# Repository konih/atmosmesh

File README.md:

<h1 align="center">AtmosMesh</h1>

<p align="center"><em>Local air sensing, connected as a mesh.</em></p>

<p align="center">

</p>

AtmosMesh is a family of local air-sensing firmware products, now spanning several product
variants (v1, Grove v1.5, Aqua, Room, Spot); none supersedes another.

## Firmware products

| Product | Product ID | Product variant | Controller | Sensor/display scope | Canonical build |
| --- | --- | --- | --- | --- | --- |
| **AtmosMesh v1** — **ARCHIVED** (D-034; physical station disassembled 2026-08-31) | `atmosmesh-v1` | `esp32-full-station` | ESP32-WROOM-32 | Full station: SSD1306, BMP280, AM2302, SDS011, MQ135, PIR/beeper, optional VEML7700, MQTT | `task build-v1` (not part of `task build-all`) |
| **AtmosMesh Grove v1.5** | `atmosmesh-grove-v1.5` | `atmosmesh-v1.5` | ESP8266EX / 4 MB NodeMCU-style board | Compact node: 128×32 SSD1306, BMP180, DHT11, uncalibrated D7 RC light, D0/D6 status LED, duty-cycled raw YL-38 ADC, MQTT | `task build-v1-5` |

The products share one PlatformIO project and host-tested core, with explicit composition roots
instead of copied firmware trees. See [ADR-0001](docs/adr/0001-multi-product-firmware-composition.md).

AtmosMesh v1 is **archived, not deleted** ([D-034](agent-context/decisions.md)): the physical
station was disassembled and its code/mentions are retired from the live fleet, but the source,
its tests, and the shared MQTT contract/composition pattern it established remain in the repo.
It was never a finished product — its wiring was never fully approved for unattended or
mains-powered use — and it is **not** a certified health, fire, gas, or life-safety instrument.

## AtmosMesh v1 measurements

| Sensor | Quantity | Notes |
| --- | --- | --- |
| SDS011 | PM2.5, PM10 | UART2 only (GPIO16/17). 5 V heater, 3.3 V UART |
| AM2302 / DHT22 | Temperature, humidity | GPIO18, 3V3 |
| BMP280 | Pressure, temperature | I²C 0x76 on GPIO21/19, 3V3 |
| Mini OLED (D-001) | Local live page | I²C 0x3C, SDA GPIO5, SCL GPIO4, **3V3 only** |
| MQ135 | Relative gas trend | Analog GPIO34 through a divider. **Never labelled CO₂ or ppm** |
| VEML7700 | Illuminance | Optional, I²C 0x10 on the BMP280 bus. Not fitted yet |
| PIR + beeper | Occupancy cue | GPIO33 / GPIO25 |

```text
SDS011 ─┐
AM2302 ─┤
BMP280 ─┼─> ESP32 ── OLED (local)
MQ135  ─┤       └─ MQTT (planned) ──> Mosquitto ──> Home Assistant
VEML   ─┘                         └─ metrics ─> Prometheus ─> Grafana
```

## Safety (read this first)

- ESP32 GPIOs and the `3V3` pin are **not 5 V tolerant**.
- SDS011 and MQ135 take **5 V power**; their *signals* stay at 3.3 V.
- SDS011 is **UART2 only**. Never GPIO1/TX0 or GPIO3/RX0 — those are the USB-UART
  used by `task flash` / `task monitor`.
- MQ135 analog goes through a measured divider before GPIO34. The live breadboard
  is 10 kΩ series + 20 kΩ to GND.
- Open mains PCBs stay off the breadboard and must be enclosed before they are
  energised. Mains switching is out of scope.
- Confirm every module's markings before you copy a pin table from this repo.

Full rules: [`AGENTS.md`](AGENTS.md) and [`docs/hardware/power.md`](docs/hardware/power.md).

## Quick start

Host tests need PlatformIO and Python 3.11 or 3.12 (not Homebrew 3.14):

```bash
task bootstrap-agent-python   # creates .venv with pyserial + esptool
task test                     # native Unity tests (no hardware)
task build-all                # both first-class product images
task build-v1                 # AtmosMesh v1 / ESP32
task build-v1-5               # AtmosMesh Grove v1.5 / ESP8266
```

Canonical device actions are `task flash-v1`, `task monitor-v1`, `task flash-v1-5`, and
`task monitor-v1-5`. Existing `build`/`flash`/`monitor` and `*-grove` tasks remain compatibility
aliases. Override the serial port with `ESP_PORT=/dev/…`.

Do not run `python -m esptool` with system Python. Direct wrapper: `./scripts/esp-tool version`.

Firmware details, OLED constructor, and the live pin map:
[`firmware/README.md`](firmware/README.md).

## Hardware

| Path | What |
| --- | --- |
| [`docs/hardware/inventory.md`](docs/hardware/inventory.md) | Confirmed parts and open questions |
| [`docs/elektronik-inventar.md`](docs/elektronik-inventar.md) | Full electronics stock inventory, including parts not currently assigned to a product |
| [`docs/hardware/datasheets/`](docs/hardware/datasheets/README.md) | Manufacturer datasheets and retained kit manuals |
| [`docs/hardware/power.md`](docs/hardware/power.md) | 5 V / 3.3 V domains |
| [`docs/hardware/oscilloscope-hantek-dso2d15.md`](docs/hardware/oscilloscope-hantek-dso2d15.md) | Bench scope: panel, probe setup, and the ripple / I²C / UART / rail recipes |
| [`hardware/kicad/`](hardware/kicad/README.md) | Bench carrier (KiCad 10): OLED, sensors, extras strip, fully routed. **Do not fabricate** until DevKit pin order is photographed |

The carrier board uses a **10 k / 15 k** MQ135 divider (3.0 V max on GPIO34).
Firmware still matches the **breadboard 10 k / 20 k** until that board replaces
the breadboard.

## Repository layout

| Path | Purpose |
| --- | --- |
| `firmware/` | One PlatformIO project, explicit product roots, shared core and native tests |
| `docs/adr/` | Architecture decision records |
| `docs/history/` | Superseded project notes and concept artifacts retained for provenance |
| `hardware/kicad/` | Bench-station carrier schematic and PCB |
| `docs/` | Architecture, hardware facts, datasheets |
| `deploy/` | Kubernetes / home-automation config (not packaged yet) |
| `tests/` | Host-side checks |
| `agent-context/` | Stories, decisions, and live session notes |
| `AGENTS.md` | Safety boundaries and workflow for humans and agents |

## Status

AtmosMesh v1 bench firmware drives the OLED (U8g2 SSD1306 ALT0), BMP280, AM2302,
SDS011 UART2, MQ135 ADC, PIR, and beeper. MQTT, Home Assistant, and the cluster
path are still ahead. Grove v1.5 hardware has runtime communication evidence for BMP180 and DHT11;
OLED controller initialization passed but pixels need visual confirmation. Cooperative D7 RC light
timing and Grove MQTT/HA discovery are implemented and host/build-tested. Reviewed Grove soil
firmware has produced two raw ADC 214 cycles about 30 seconds apart. The installed D6 red / D0
green LED is operator-confirmed common-anode; soil direction/threshold calibration, switched-rail
electrical behavior, MQTT receipt and OLED pixels remain unconfirmed
([roadmap](agent-context/roadmap.md)).

## License and contributors

[MIT](LICENSE). People: [CONTRIBUTORS.md](CONTRIBUTORS.md). Security:
[SECURITY.md](SECURITY.md).

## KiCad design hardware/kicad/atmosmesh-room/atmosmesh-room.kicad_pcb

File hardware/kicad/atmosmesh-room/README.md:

# AtmosMesh Room carrier — provisional design

**DO NOT ENERGISE THIS BOARD YET.** The controller and every module connector order are now
identified, but no supply voltage or output swing has been measured on the 5 V modules. This project is a protected, reviewable starting point, not a wiring
approval.

The controller is the **ideaspark ESP32 1.14 inch TFT LCD board** (ESP32-WROOM-32), confirmed from
[`docs/hardware/ideaspark-esp32-tft-pinout.png`](../../../docs/hardware/ideaspark-esp32-tft-pinout.png).
Its 30 pins and their order are therefore no longer provisional: pads 1–15 are the left column and
16–30 the right column, both counted from the USB/button end. What remains unmeasured is the
physical **row spacing**: 25.4 mm is still an assumption, so MEASURE THE ROW SPACING before
cutting a socket or committing a hole pattern.

**The integrated display is SPI, not I²C.** It occupies GPIO23 (MOSI), GPIO18 (SCLK), GPIO15 (CS),
GPIO2 (DC), GPIO4 (RST) and GPIO32 (backlight). GPIO21/22 carry no onboard device, so the carrier
supplies the only I²C pull-ups it has.

## Files

| File | Purpose |
| --- | --- |
| `atmosmesh-room.kicad_pro` | KiCad 10 project; open this file |
| `atmosmesh-room.kicad_sch` | Reviewable electrical contract |
| `atmosmesh-room.kicad_pcb` | **Parked.** Kept only as a netlist/silkscreen cross-check — not the build target |
| `perfboard.md` | **The build target**: 31×27 hole plan, orientation rules and build order |
| `atmosmesh-room-perfboard-drawing.svg` | Zoomable front, mirrored back and logical wiring planning drawing |
| `atmosmesh-room-perfboard-drawing.png` | Rendered preview of the planning drawing |
| `validate_room_perfboard.py` | Deterministic structural check on the perfboard plan |
| `room.pretty/`, `fp-lib-table`, `sym-lib-table` | Local THT library contract |
| `BOM.csv` | Values, fitting policy and verification notes |
| `wiring.md` | Connector contract and staged pre-power checks |
| `validate_room_carrier.py` | Deterministic structural safety check |
| `generate_project.py` | Reproducible project generator; KiCad source remains editable |
| `requirements-generator.txt` | Pinned generator-only Python dependency |

## Safety architecture

- ESP32 GPIO and `3V3` must **never receive 5 V**.
- **Never wire GPIO23, 18, 15, 2, 4 or 32** — the dev board's own TFT drives them. GPIO12 is the
  flash-voltage strap (high at boot can stop the board starting) and GPIO1/GPIO3 are the CP2102
  USB-UART used by `task flash` and `task monitor`. `generate_project.py` refuses to emit a net on
  any of them and `validate_room_carrier.py` fails if one appears.
- GPIO21/SDA and GPIO22/SCL reach the external sensor branch through 330 Ω series resistors. Those
  resistors limit fault current and damp edges; they are not a measurement noise source.
- `R_PU_SDA` and `R_PU_SCL` (3.3 kΩ to 3.3 V) are the bus pull-ups. They are required because the
  display is SPI: nothing on the controller board pulls I²C up. They sit on the sensor side of the
  330 Ω resistors so the series resistance stays a fault limit rather than part of the pull-up
  divider. With both breakouts populated the parallel result is roughly 2.0 kΩ, about 1.6 mA at
  3.3 V, inside the I²C 3 mA sink limit, so they stay fitted rather than DNP. Every resistor value
  on this board is justified in `wiring.md`'s sizing table.
- Both sensors receive direct 3.3 V and local 220 nF decoupling. There is deliberately no diode or
  resistor in a sensor supply: a breakout's pull-ups reference its own VDD, so dropping sensor VDD
  drags the pull-ups down with it and buys nothing, while adding a droop path under the SHT41's
  measurement current bursts. The build uses 100 nF for `C1`, `C3`, `C4`
  and `C7` — the confirmed ceramic stock value, inside D-022's own 47–220 nF range.
- The confirmed five-pin VEML7700 connector is `VIN`, `3Vo`, `GND`, `SCL`, `SDA`: `VIN` receives
  3.3 V and `3Vo` is regulator output and remains NC.
- PIR power can come only from a confirmed USB/5 V pin, through `JP_PIR_5V` which is **DEFAULT
  OPEN**, then a 1N5819. PIR OUT drives a 2N3904 through 10 kΩ; GPIO33 sees only the collector and a
  10 kΩ pull-up to 3.3 V. Motion logic is active-low.
- The buzzer is a confirmed Keyes 3-pin module, header order `S`/`VCC`/`−`. GPIO25 drives `S`
  directly through `R_BEEP_S` 100 Ω, active HIGH, exactly as AtmosMesh v1 drives the same part. The
  low-side NPN and flyback diode are gone because the transducer is **self-oscillating inside the
  can** — the breakout PCB carries no parts, so the middle `VCC` pin is a no-op and GPIO25 sources
  the whole operating current. The evidence is that v1 sounds this part with a bare 50 ms DC
  `digitalWrite(HIGH)`, which neither a piezo disc nor a passive coil can do. That type is inferred,
  not measured: one ohmmeter reading across `S` and `−` settles it, and `R_BEEP_S` is **never
  raised** — see the table in `wiring.md` before changing anything.
- `JP_5V_SRC` selects where `+5V_DOMAIN` comes from: the board's `VIN` (pins 1–2) or an external
  bench supply on `J_5V_EXT` (pins 2–3). A 3-pin header takes exactly one shunt, so the two sources
  can never be bridged back into the host's USB port. Use the external, current-limited supply for
  first power-up and whenever the SDS011 fan runs.
- The SDS011 takes 5 V through `JP_SDS_5V`, **DEFAULT OPEN**, with **no series diode**: its minimum
  is 4.7 V and a Schottky at fan current drops below that. Its UART is crossed — sensor TXD to
  GPIO16/RX2, GPIO17/TX2 to sensor RXD — each through a 1 kΩ series resistor that bounds a driver
  fight to about 3.3 mA. The generator refuses both a straight-through UART and a diode on that
  rail.
- Three indicator LEDs show which domains are live. `D_LED_SDS` and `D_LED_PIR` draw **through**
  their own default-open jumpers, so a lit LED is direct evidence that the jumper it reports on is
  closed. Use red or green: a blue or white LED's ~3.0 V forward drop leaves too little across
  `R_LED_3V3` on the 3.3 V rail.
- No Zener clamp is used. This is now positively evidenced rather than assumed: the Zener
  assortment in `docs/elektronik-inventar.md` is the 1N47xx series starting at **1N4733 = 5.1 V**,
  which clamps far too late to protect a 3.3 V GPIO. A 3.3 V part (1N4728) is not held.

## The build target is perfboard

The operator builds this by hand on a **31 × 27 hole** perfboard, so no board is fabricated. The
schematic is the electrical contract and [`perfboard.md`](perfboard.md) is the build plan.

`atmosmesh-room.kicad_pcb` is **parked**: it is still generated from the netlist and still carries
the safety silkscreen, which is why its checks remain in `validate_room_carrier.py`, but its
placement is not maintained as a fabrication candidate. Do not order it.

## Placement and routing state

The VEML7700 sits at a board edge and must be optically shielded from the TFT backlight. The SHT41 sits at
the opposite ventilated edge, away from the ESP32 regulator, PIR electronics and buzzer. The 5 V
PIR block is fenced at the right edge. The antenna clearance is marked on `User.Drawings` and silk;
its final copper keepout/overhang cannot be fixed until the exact board orientation is photographed.

Copper is intentionally unrouted because the Ideaspark row spacing and orientation, plus each
module connector order, are unverified. This prevents a plausible-looking provisional drawing
from being mistaken for a fabrication-ready board. Do not "finish the ratsnest" by assuming a
generic ESP32 DevKit image.

The complete net table, double-sided through-hole placement guidance, assembly order, unpowered
checks, staged commissioning and stop conditions are in [`wiring.md`](wiring.md).

## Validation

From this directory:

```sh
python3.12 -m venv .generator-venv
.generator-venv/bin/pip install -r requirements-generator.txt
.generator-venv/bin/python generate_project.py
python3 validate_room_carrier.py
kicad-cli sch erc --severity-all --exit-code-violations \
  -o atmosmesh-room-erc.rpt atmosmesh-room.kicad_sch
kicad-cli pcb drc --severity-all --schematic-parity --refill-zones \
  -o atmosmesh-room-drc.rpt atmosmesh-room.kicad_pcb
kicad-cli sch export pdf -o atmosmesh-room-schematic.pdf atmosmesh-room.kicad_sch
```

DRC reports the deliberately unrouted nets as unconnected; schematic parity must remain clean and
there must be no other DRC violation. Routing stays blocked until the exact physical parts are
verified.

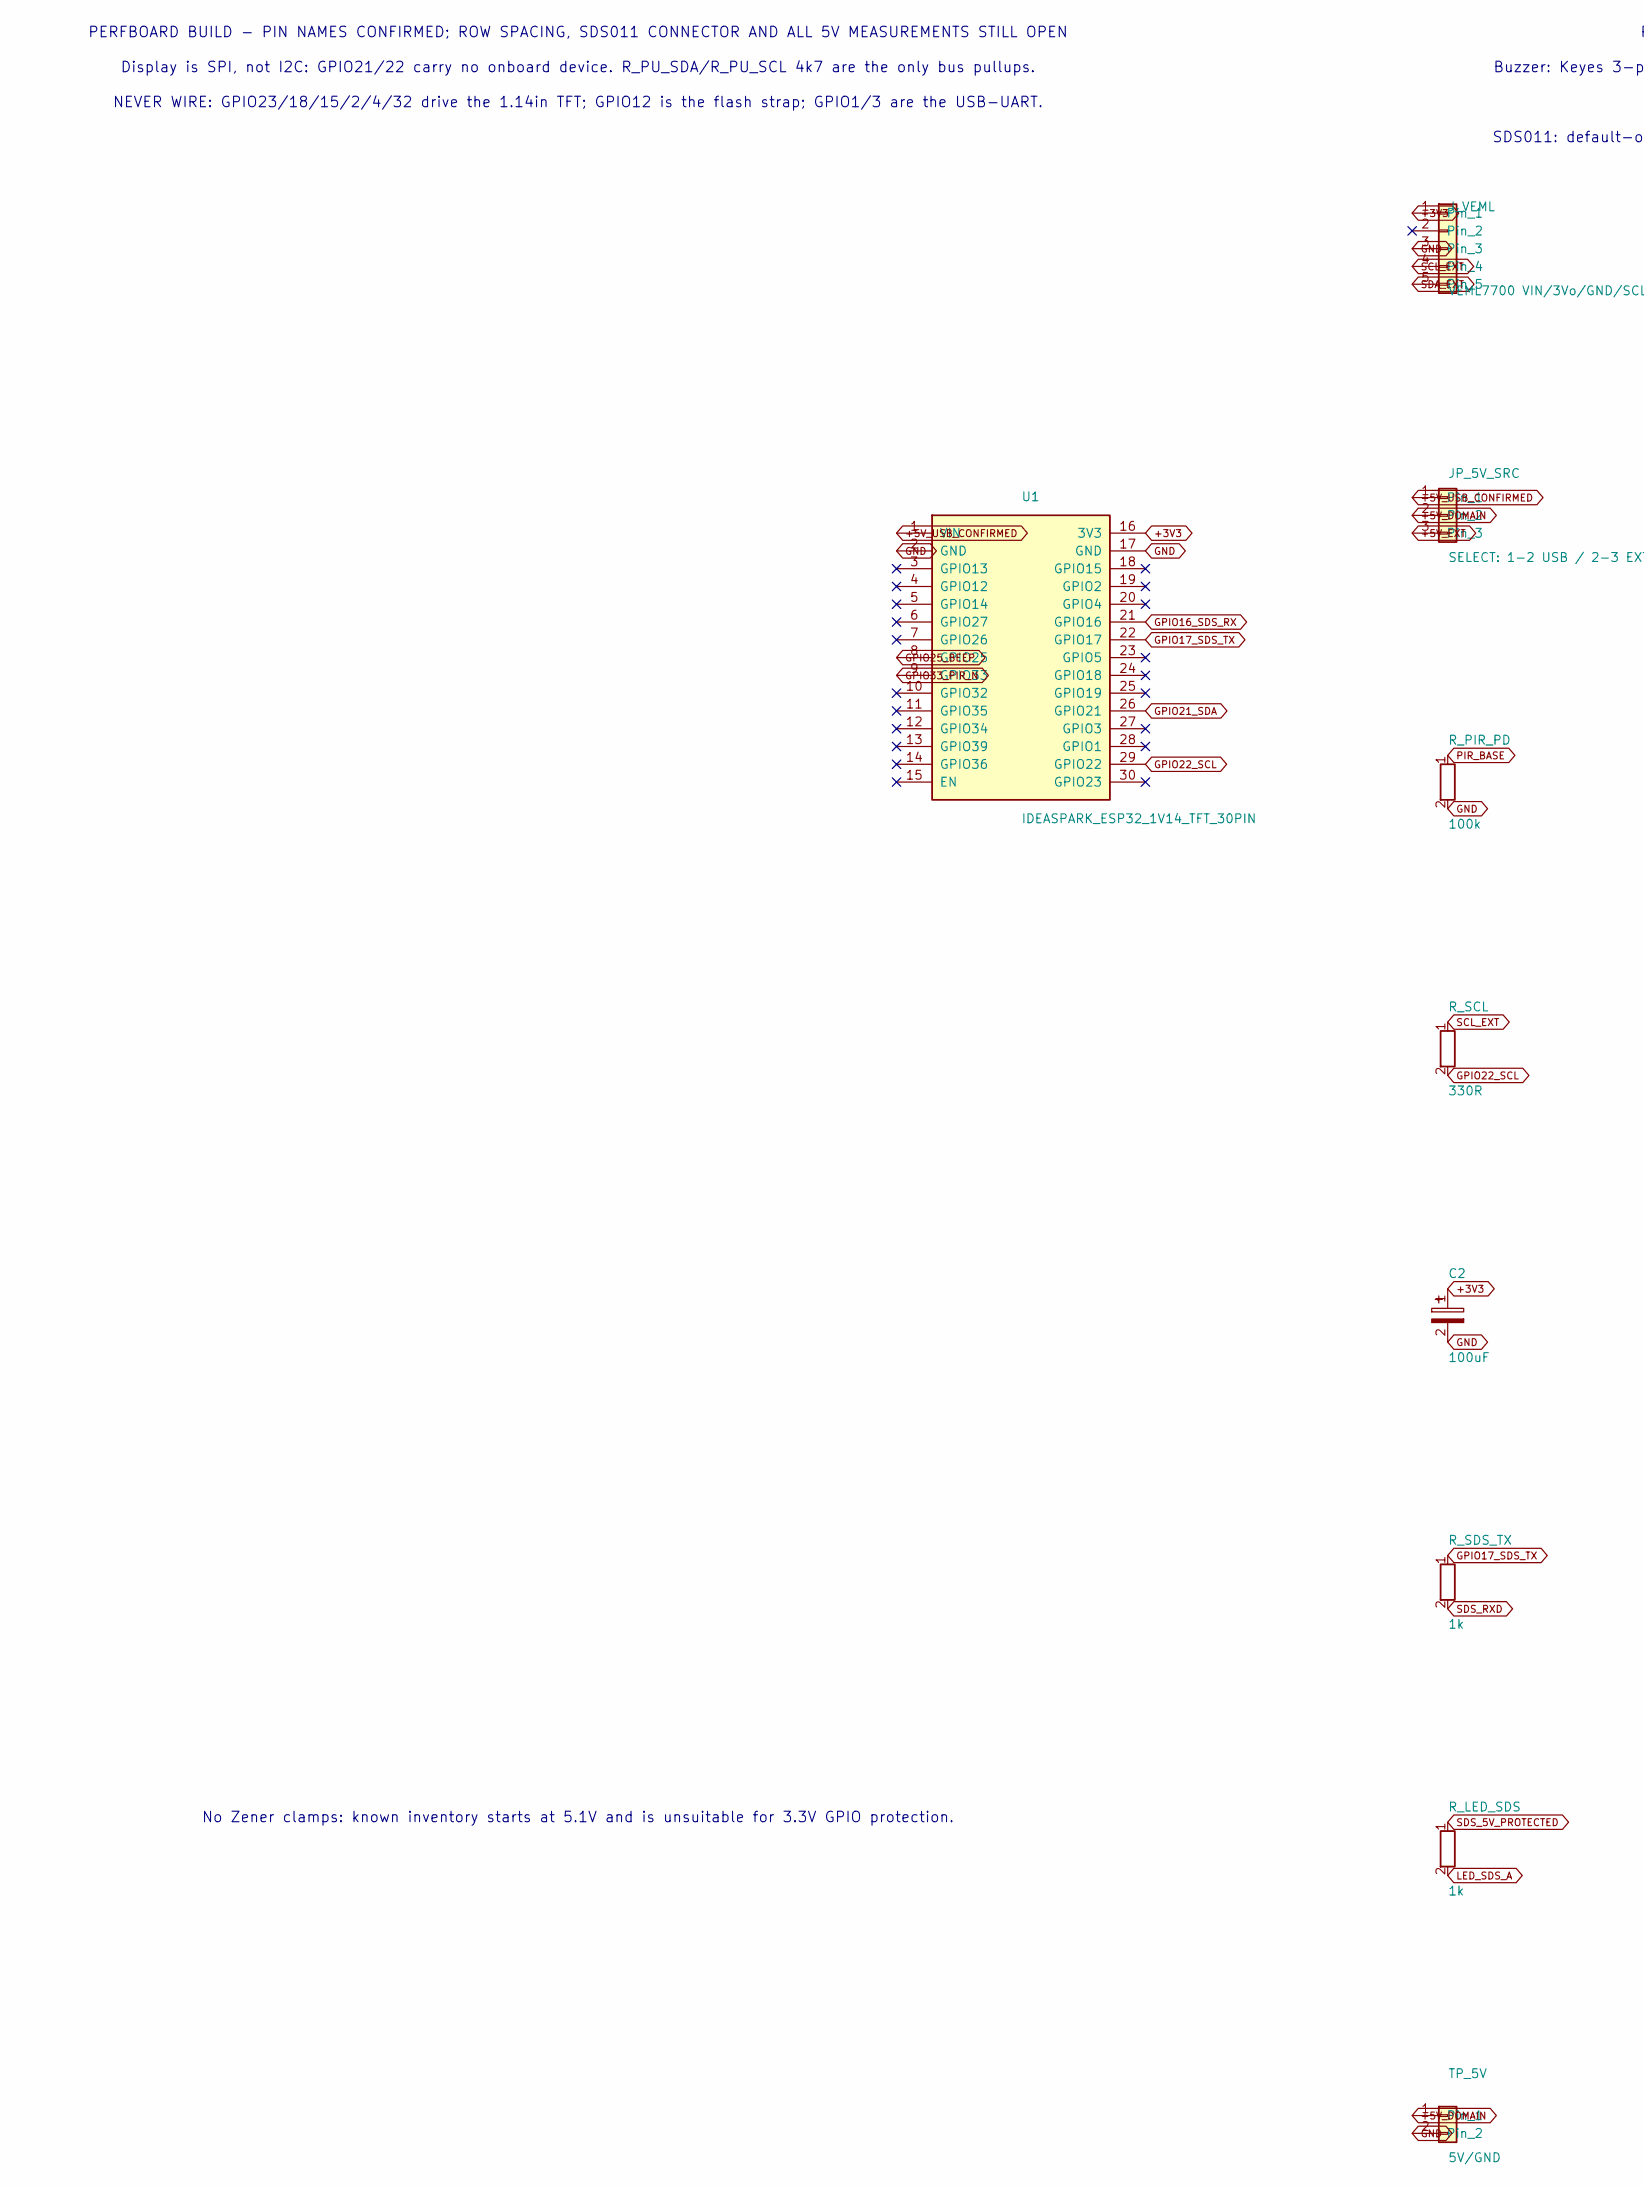
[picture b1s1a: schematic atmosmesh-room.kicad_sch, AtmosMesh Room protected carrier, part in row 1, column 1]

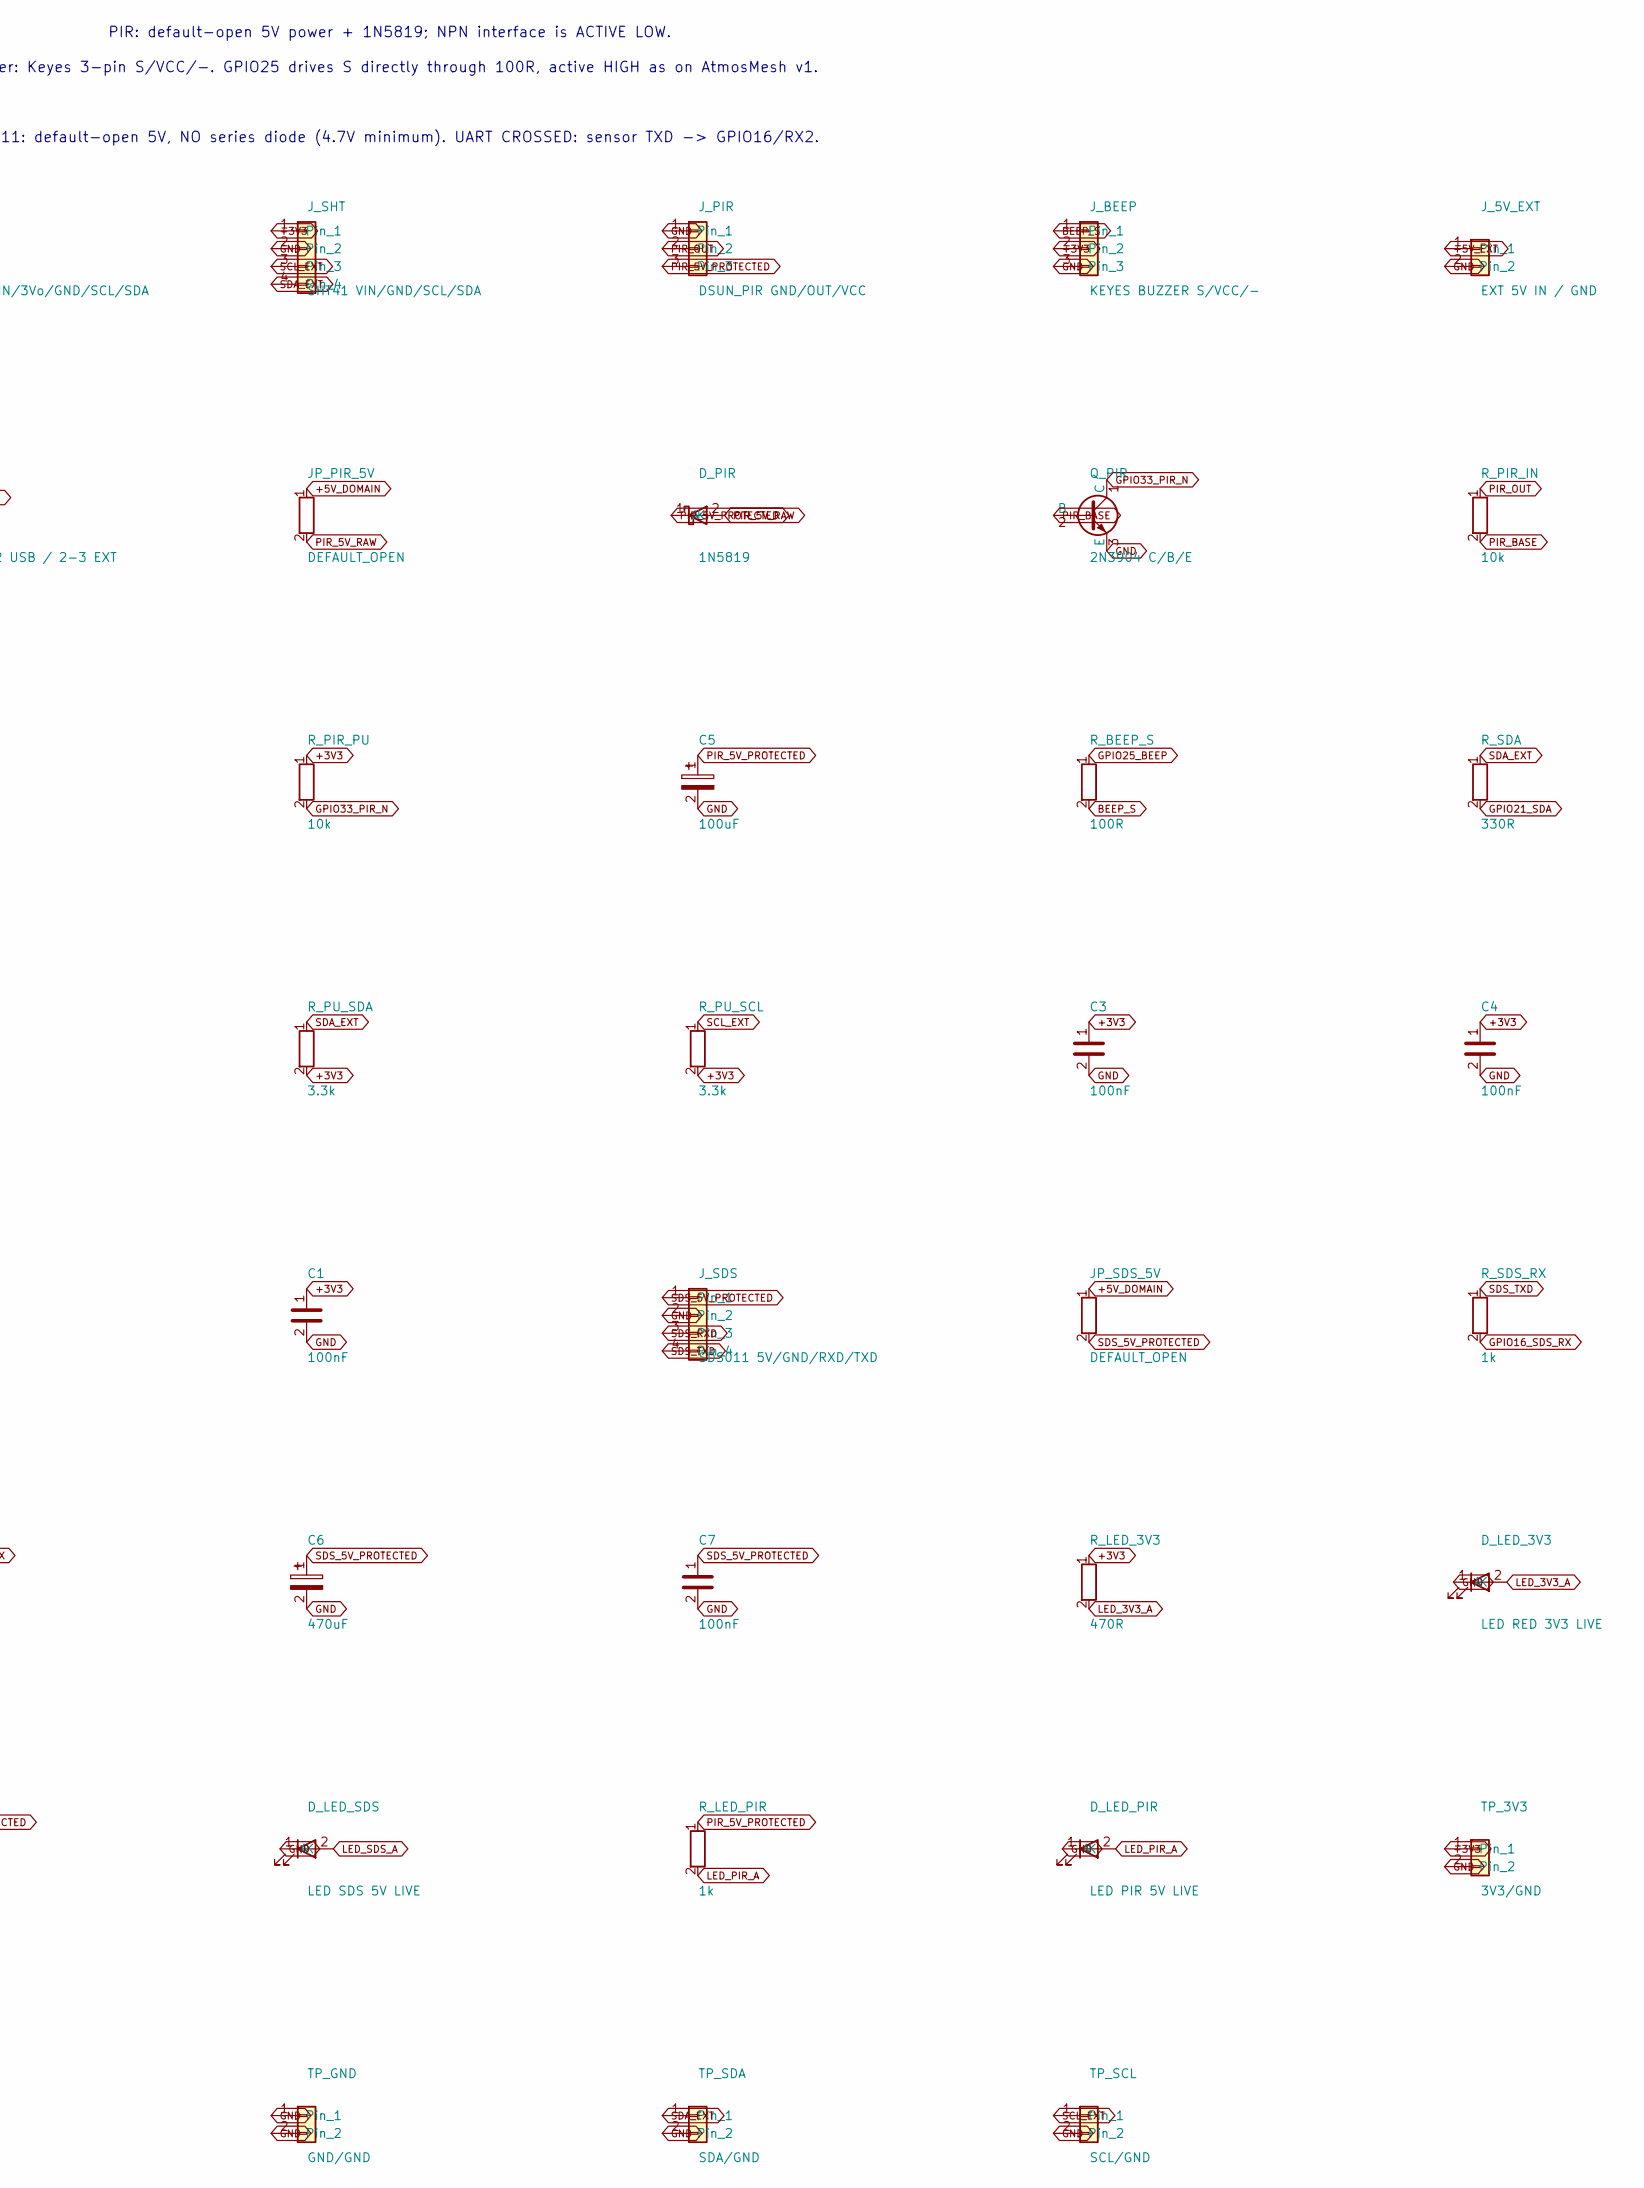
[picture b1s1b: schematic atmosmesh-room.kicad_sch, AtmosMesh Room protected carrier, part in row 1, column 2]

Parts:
C1, C3, C4, C7: 100nF; C_Disc_P5.00mm
C2, C5: 100uF; C_Radial_P2.00mm
C6: 470uF; C_Radial_P2.00mm
D_LED_3V3: LED RED 3V3 LIVE; D_Axial_P7.62mm
D_LED_PIR: LED PIR 5V LIVE; D_Axial_P7.62mm
D_LED_SDS: LED SDS 5V LIVE; D_Axial_P7.62mm
D_PIR: 1N5819; D_Axial_P7.62mm
JP_5V_SRC: SELECT: 1-2 USB / 2-3 EXT; PinHeader_1x03_P2.54mm
JP_PIR_5V: DEFAULT_OPEN; Jumper_2_Open_P2.54mm
JP_SDS_5V: DEFAULT_OPEN; Jumper_2_Open_P2.54mm
J_5V_EXT: EXT 5V IN / GND; PinHeader_1x02_P2.54mm
J_BEEP: KEYES BUZZER S/VCC/-; PinHeader_1x03_P2.54mm
J_PIR: DSUN_PIR GND/OUT/VCC; PinHeader_1x03_P2.54mm
J_SDS: SDS011 5V/GND/RXD/TXD; PinHeader_1x04_P2.54mm
J_SHT: SHT41 VIN/GND/SCL/SDA; PinHeader_1x04_P2.54mm
J_VEML: VEML7700 VIN/3Vo/GND/SCL/SDA; PinHeader_1x05_P2.54mm
Q_PIR: 2N3904 C/B/E; TO92_CBE
R_BEEP_S: 100R; R_Axial_P7.62mm
R_LED_3V3: 470R; R_Axial_P7.62mm
R_LED_PIR: 1k; R_Axial_P7.62mm
R_LED_SDS: 1k; R_Axial_P7.62mm
R_PIR_IN: 10k; R_Axial_P7.62mm
R_PIR_PD: 100k; R_Axial_P7.62mm
R_PIR_PU: 10k; R_Axial_P7.62mm
R_PU_SCL: 3.3k; R_Axial_P7.62mm
R_PU_SDA: 3.3k; R_Axial_P7.62mm
R_SCL: 330R; R_Axial_P7.62mm
R_SDA: 330R; R_Axial_P7.62mm
R_SDS_RX: 1k; R_Axial_P7.62mm
R_SDS_TX: 1k; R_Axial_P7.62mm
TP_3V3: 3V3/GND; TestPoint_2Pin_THT
TP_5V: 5V/GND; TestPoint_2Pin_THT
TP_GND: GND/GND; TestPoint_2Pin_THT
TP_SCL: SCL/GND; TestPoint_2Pin_THT
TP_SDA: SDA/GND; TestPoint_2Pin_THT
U1: IDEASPARK_ESP32_1V14_TFT_30PIN; Ideaspark_30Pin_Provisional

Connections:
+3V3: C1.1, C2.1, C3.1, C4.1, J_BEEP.2, J_SHT.1, J_VEML.1, R_LED_3V3.1, R_PIR_PU.1, R_PU_SCL.2, R_PU_SDA.2, TP_3V3.1, U1.16 (3V3)
+5V_DOMAIN: JP_5V_SRC.2, JP_PIR_5V.1, JP_SDS_5V.1, TP_5V.1
+5V_EXT: JP_5V_SRC.3, J_5V_EXT.1
+5V_USB_CONFIRMED: JP_5V_SRC.1, U1.1 (VIN)
BEEP_S: J_BEEP.1, R_BEEP_S.2
GND: C1.2, C2.2, C3.2, C4.2, C5.2, C6.2, C7.2, D_LED_3V3.1 (K), D_LED_PIR.1 (K), D_LED_SDS.1 (K), J_5V_EXT.2, J_BEEP.3, J_PIR.1, J_SDS.2, J_SHT.2, J_VEML.3, Q_PIR.3 (E), R_PIR_PD.2, TP_3V3.2, TP_5V.2, TP_GND.1, TP_GND.2, TP_SCL.2, TP_SDA.2, U1.2 (GND), U1.17 (GND)
GPIO16_SDS_RX: R_SDS_RX.2, U1.21 (GPIO16)
GPIO17_SDS_TX: R_SDS_TX.1, U1.22 (GPIO17)
GPIO21_SDA: R_SDA.2, U1.26 (GPIO21)
GPIO22_SCL: R_SCL.2, U1.29 (GPIO22)
GPIO25_BEEP: R_BEEP_S.1, U1.8 (GPIO25)
GPIO33_PIR_N: Q_PIR.1 (C), R_PIR_PU.2, U1.9 (GPIO33)
LED_3V3_A: D_LED_3V3.2 (A), R_LED_3V3.2
LED_PIR_A: D_LED_PIR.2 (A), R_LED_PIR.2
LED_SDS_A: D_LED_SDS.2 (A), R_LED_SDS.2
PIR_5V_PROTECTED: C5.1, D_PIR.1 (K), J_PIR.3, R_LED_PIR.1
PIR_5V_RAW: D_PIR.2 (A), JP_PIR_5V.2
PIR_BASE: Q_PIR.2 (B), R_PIR_IN.2, R_PIR_PD.1
PIR_OUT: J_PIR.2, R_PIR_IN.1
SCL_EXT: J_SHT.3, J_VEML.4, R_PU_SCL.1, R_SCL.1, TP_SCL.1
SDA_EXT: J_SHT.4, J_VEML.5, R_PU_SDA.1, R_SDA.1, TP_SDA.1
SDS_5V_PROTECTED: C6.1, C7.1, JP_SDS_5V.2, J_SDS.1, R_LED_SDS.1
SDS_RXD: J_SDS.3, R_SDS_TX.2
SDS_TXD: J_SDS.4, R_SDS_RX.1

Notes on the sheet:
PERFBOARD BUILD - PIN NAMES CONFIRMED; ROW SPACING, SDS011 CONNECTOR AND ALL 5V MEASUREMENTS STILL OPEN
Display is SPI, not I2C: GPIO21/22 carry no onboard device. R_PU_SDA/R_PU_SCL 4k7 are the only bus pullups.
NEVER WIRE: GPIO23/18/15/2/4/32 drive the 1.14in TFT; GPIO12 is the flash strap; GPIO1/3 are the USB-UART.
No Zener clamps: known inventory starts at 5.1V and is unsuitable for 3.3V GPIO protection.
PIR: default-open 5V power + 1N5819; NPN interface is ACTIVE LOW.
SDS011: default-open 5V, NO series diode (4.7V minimum). UART CROSSED: sensor TXD -> GPIO16/RX2.
Buzzer: Keyes 3-pin S/VCC/-. GPIO25 drives S directly through 100R, active HIGH as on AtmosMesh v1.

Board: 2 copper layers, 44 parts (0 on the bottom side), 24 nets, no tracks yet.

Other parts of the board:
H1, H2, H3, H4: M3; MountingHole_3.2mm_M3

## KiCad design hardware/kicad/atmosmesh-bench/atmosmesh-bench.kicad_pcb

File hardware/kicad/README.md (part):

# AtmosMesh bench station — KiCad PCB

A 2-layer, all-through-hole carrier board for the **bench** revision: an ESP32-WROOM-32 DevKit sits
in two 1×15 sockets, the three 3.3 V sensors get proper connectors, and the future 5 V sensors get
connectors in a visually and electrically separated block. **No mains on this board** — the AC/DC
module stays off-board and enclosed ([`docs/hardware/power.md`](../../docs/hardware/power.md)).

Board outline is **139 × 58 mm**, 1.6 mm, 2 copper layers, GND poured on both.

## Files

| Path | What it is |
| --- | --- |
| `atmosmesh-bench/atmosmesh-bench.kicad_pro` | Project file — open this one |
| `atmosmesh-bench/atmosmesh-bench.kicad_sch` | Single-sheet schematic (A3) with named nets |
| `atmosmesh-bench/atmosmesh-bench.kicad_pcb` | Board: placement, netlist, outline, keepout, GND pours |
| `atmosmesh-bench/atmosmesh.kicad_sym` | Project symbol library (all symbols, vendored) |
| `atmosmesh-bench/atmosmesh.pretty/` | Project footprint library (all footprints, vendored) |
| `atmosmesh-bench/sym-lib-table`, `fp-lib-table` | Point the project at those two libraries |
| `atmosmesh-bench/atmosmesh-bench-schematic.pdf` | Rendered schematic, for review without KiCad |

## Opening it

Written in **KiCad 9 file format** (`.kicad_sch` 20250114, `.kicad_pcb` 20241229,
`.kicad_sym` 20241209) and validated with **KiCad 10.0.5**. Opens in KiCad 9 and 10.

```sh
open -a KiCad hardware/kicad/atmosmesh-bench/atmosmesh-bench.kicad_pro
```

Every symbol and footprint is **vendored into the project** (`atmosmesh:*`), so nothing depends on a
global library table — the project opens, ERCs and DRCs identically on any machine. The geometry of
the standard parts is copied verbatim from the KiCad 10.0.5 stock libraries; only the ESP32 DevKit
socket is original.

## Authoritative pin map (operator, 2026-08-14)

This is the **rewired bench** map. It supersedes every earlier D2/GPIO18 arrangement.

| Function | ESP32 pin | Net | Socket pin | Connector |
| --- | --- | --- | --- | --- |
| OLED 0x3C I²C **SDA** (D-001) | **GPIO5** (D5) | `SDA_LCD` | U1.23 | J1.3 |
| OLED 0x3C I²C **SCL** (D-001) | **GPIO4** (D4) | `SCL_LCD` | U1.26 | J1.4 |
| OLED VCC / GND | — | `+3V3` / `GND` | U1.30 / U1.29 | J1.2 / J1.1 |
| BMP280 **SDA** | **GPIO21** | `SDA_SENS` | U1.20 | J2.4 |
| BMP280 **SCL** | **GPIO19** (D19) | `SCL_SENS` | U1.21 | J2.3 |
| BMP280 **CSB** → 3V3 (I²C mode) | — | `+3V3` | — | J2.5 |
| BMP280 **SDO** → GND (addr **0x76**) | — | `GND` | — | J2.6 |
| BMP280 VCC | — | `+3V3` | U1.30 | J2.1 |
| AM2302 / DHT22 **DATA** | **GPIO18** (D18) | `DHT_DATA` | U1.22 | J3.2 |
| AM2302 VDD / GND | — | `+3V3` / `GND` | — | J3.1 / J3.3 |
| SDS011 TXD → ESP32 RX2 | GPIO16 | `PM_TX` | U1.25 | J4.3 |
| SDS011 RXD ← ESP32 TX2 | GPIO17 | `PM_RX` | U1.24 | J4.4 |
| MQ135 analog out | — | `MQ_AOUT` | — | J5.3 → R2 |
| MQ135 divider output | GPIO34 (ADC1, input-only) | `MQ_ADC` | U1.4 | R2/R3 |
| DevKit `VIN`, through JP1 | — | `ESP_VIN` | U1.15 | JP1.2 |
| Beeper **SIG** | **GPIO25** | `BEEP_SIG` | U1.8 | J_BEEP.3 |
| Beeper VCC (3V3 default, JP_BEEP → +5V) | — | `BEEP_VCC` | — | J_BEEP.1 / JP_BEEP.2 |
| PIR D-SUN **SIG** (digital in, **not 27**) | **GPIO33** | `PIR_OUT` | U1.7 | J_PIR.3 |
| PIR VCC (3V3 default, JP_PIR → +5V for HC-SR501) | — | `PIR_VCC` | — | J_PIR.1 / JP_PIR.2 |
| VEML7700 lux **SCL** (shared sensor bus) | **GPIO19** | `SCL_SENS` | U1.21 | J_VEML.3 |
| VEML7700 lux **SDA** (shared sensor bus, addr 0x10) | **GPIO21** | `SDA_SENS` | U1.20 | J_VEML.4 |
| VEML7700 VCC / GND (3V3 only) | — | `+3V3` / `GND` | — | J_VEML.1 / J_VEML.2 |
| **GPIO2** | **GPIO2** | *no-connect* | U1.27 | — |

`R1` is the **10 kΩ pull-up from `DHT_DATA` to `+3V3`**. `R4`/`R5` are optional 4k7 pull-ups on the
sensor I²C bus, fitted as **DNP** because the GY-BMP280 breakout already carries pull-ups.

### Named nets

`+3V3` `+5V` `GND` `ESP_VIN` · `SDA_LCD` `SCL_LCD` · `SDA_SENS` `SCL_SENS` · `DHT_DATA` ·
`PM_TX` `PM_RX` · `MQ_AOUT` `MQ_ADC` · `LED_A` ·
`BEEP_VCC` `BEEP_SIG` · `PIR_VCC` `PIR_OUT`

Signals use **global labels**, so the board net names match the sheet exactly (no `/` prefix).
Deliberately unused pins carry no-connect flags and therefore appear as KiCad's
`unconnected-(…)` nets on the board — that is intended, not an omission.

### J7 — 3.3 V flying-lead harness

An alternative to the socket: bring the DevKit in on jumper wires if its pin order turns out to
differ from the assumption below. **Populate U1 or J7, never both.**

| 1 | 2 | 3 | 4 | 5 | 6 | 7 | 8 | 9 | 10 | 11 | 12 |
| --- | --- | --- | --- | --- | --- | --- | --- | --- | --- | --- | --- |
| +3V3 | GND | GPIO4 | GPIO5 | GPIO18 | GPIO19 | GPIO21 | GPIO16 | GPIO17 | GPIO34 | GND | +3V3 |

### Extras strip — J_BEEP / J_PIR / J_VEML (2026-08-14)

Live extras from the breadboard (`agent-context/extra-peripherals.md`), placed in their own silk
box at the right board edge. `J_BEEP` and `J_PIR` are **1×3, pin order VCC / GND / SIG**; SIG is
always 3.3 V. `J_BEEP` (silk `BEEPER`, SIG=GPIO25) and `J_PIR` (silk `D-SUN PIR`, SIG=GPIO33 —
**not 27**) get a 3-pin VCC-select jumper (`JP_BEEP` / `JP_PIR`: 1=+3V3 default, 2=VCC out,
3=+5V — 5 V position only for 5 V-powered modules). `J_VEML` (silk `VEML7700 LUX`) is a 1×4
VCC/GND/SCL/SDA header on the **shared sensor I²C bus** (GPIO21/GPIO19, same bus as the BMP280;
VEML7700 addr 0x10, BMP280 0x76 — no clash), 3V3-only. The HC-20/DC-20 mic was removed from the
bench (2026-08-14); GPIO22 and GPIO35 are free. **No J_TFT** — the colour TFT was dropped.

## Electrical rules built into the board

1. **No 5 V on any ESP32 GPIO or on `+3V3`.** The 5 V nets touch only J6 (input), J4/J5 (future
   sensors), C1/C4, R6/D1, JP1, and pin 3 of the VCC-select jumpers JP_BEEP / JP_PIR. **Common GND
   only** — the two domains share nothing else. The jumpers feed module **power** only; SIG pins
   are always 3.3 V.
2. `+3V3` is an **output** of the DevKit's onboard LDO (U1.30). Nothing back-feeds it; the 3.3 V AC/DC
   spare must not be paralleled onto it.
3. **`JP1` stays OPEN on the bench.** It is the only path from the 5 V rail to the DevKit `VIN`.
   Close it only after the AC/DC module has been measured and enclosed, and **never together with
   USB** — USB/VIN coexistence on this board is unverified.
4. The 5 V block is fenced off on the silkscreen (`5V DOMAIN - NEVER TO A GPIO`) and sits in the
   bottom-right corner, physically away from the 3.3 V connectors.
5. `MQ135` on the schematic still shows `R2`/`R3` as 10 k / 15 k (3.0 V at 5.0 V in). The **live
   bench** (2026-08-14) is **10 kΩ series + 20 kΩ to GND** → 3.33 V at 5.0 V AOUT, **no GPIO
   headroom**. Firmware logs that warning. Never put 5 V on GPIO34, and never label MQ135 as CO₂.

### GPIO2

**GPIO2 is left free and unconnected** — it is a download strap and must stay unloaded so USB
flashing works without unplugging anything. There is no display jumper any more: the display (OLED,
D-001) moved to GPIO5/GPIO4, so the old "unplug to flash" workaround is gone. GPIO5 is also a
strap, but the module's I²C pull-up keeps it idle-high, which is the correct boot level.

## Before you fabricate: verify the DevKit pin order

The DevKit's silkscreen has **not been photographed yet**
([`docs/hardware/inventory.md`](../../docs/hardware/inventory.md) still lists the board name and pin
labels as unconfirmed). `U1` assumes the common DOIT-style 30-pin order, USB at the `+Y` end:

- **Left row, pins 1–15:** EN, GPIO36/VP, GPIO39/VN, GPIO34, GPIO35, GPIO32, GPIO33, GPIO25, GPIO26,
  GPIO27, GPIO14, GPIO12, GPIO13, GND, VIN
- **Right row, pins 16–30:** GPIO23, GPIO22, GPIO1/TX0, GPIO3/RX0, GPIO21, GPIO19, GPIO18, GPIO5,
  GPIO17/TX2, GPIO16/RX2, GPIO4, GPIO2, GPIO15, GND, 3V3

The board also carries `VERIFY DEVKIT PINOUT / GPIO2 FREE` on the front silkscreen. If the physical
board differs, fix `U1`'s pin names in `atmosmesh.kicad_sym` (the footprint pads are positional, so
only the symbol mapping changes) — or ignore the socket and wire through **J7**. Two row spacings are
provided: `ESP32_DevKit_1x15x2_P25.40mm` (placed) and `ESP32_DevKit_1x15x2_P22.86mm` (0.9 in
variants).

## State of the board — placed AND routed

The board is **fully routed**: all signal and power nets are on copper, GND is carried by the
poured zones on `F.Cu` and `B.Cu` (fills are saved in the file). Routing was generated
programmatically (grid router, 0.25/0.32 mm clearance, 0.4 mm signals / 0.6 mm power per the
netclasses) and verified with KiCad DRC: **0 violations at all severities, 0 unconnected items,
0 schematic parity issues**. 27 vias total; B.Cu carries short crossings only, so the ground
plane stays largely intact.

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
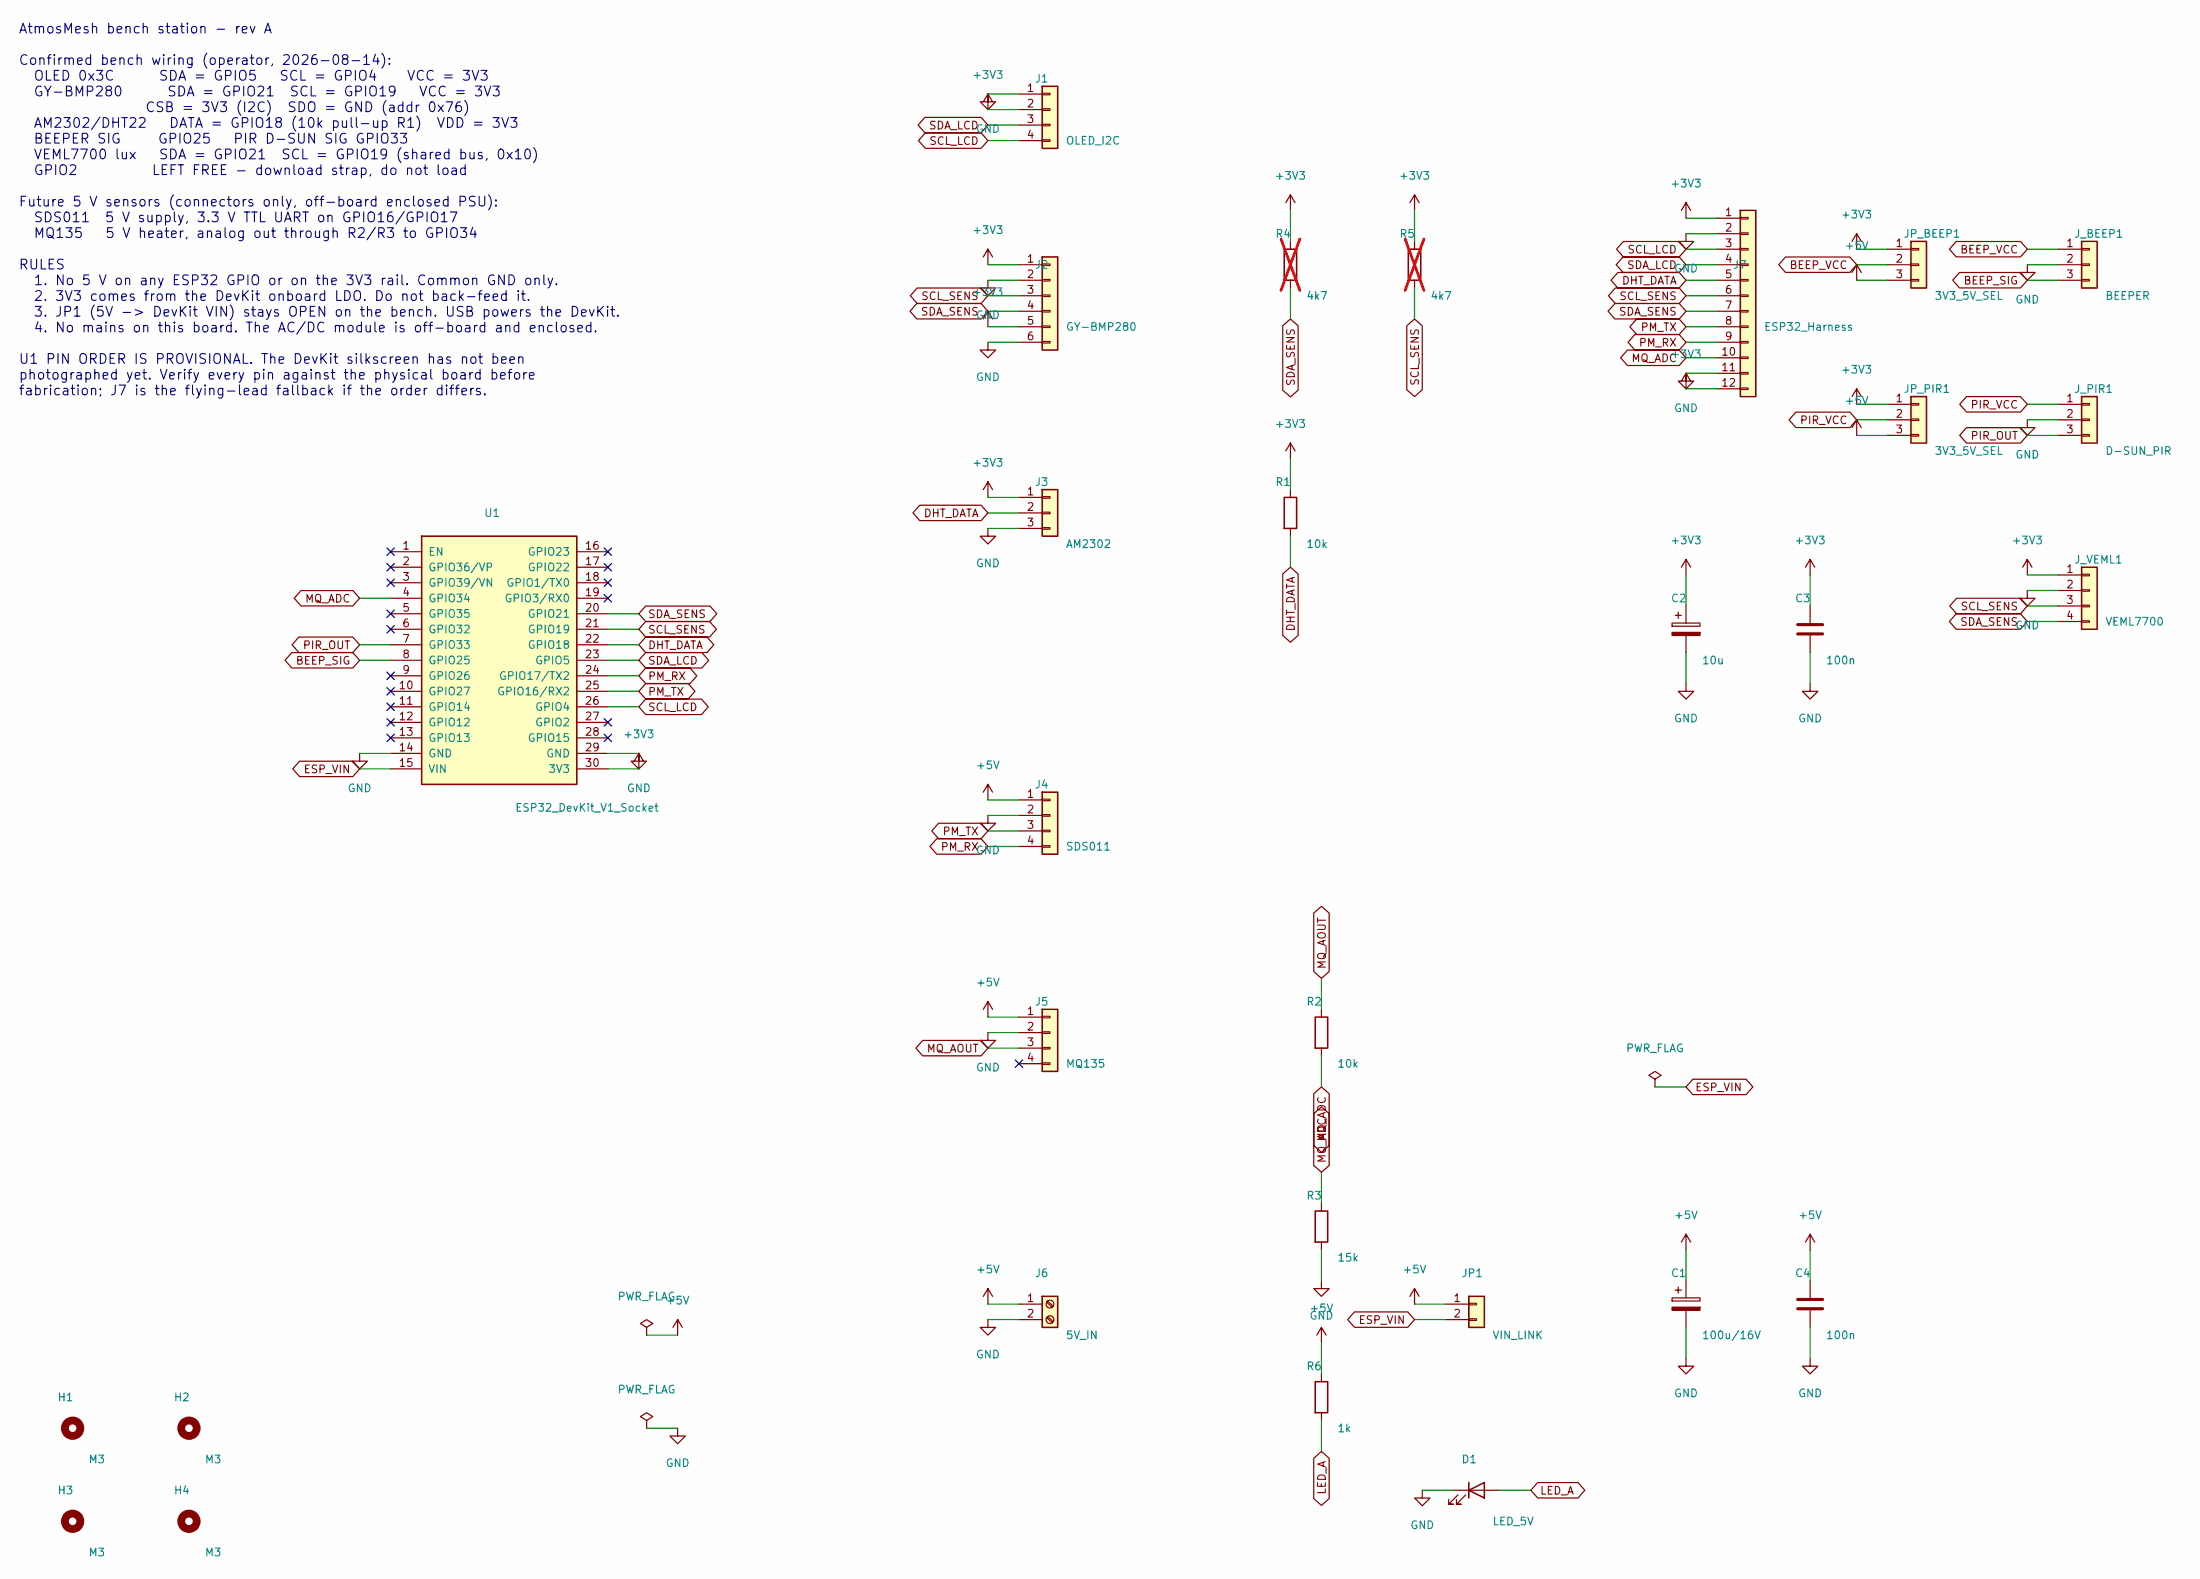
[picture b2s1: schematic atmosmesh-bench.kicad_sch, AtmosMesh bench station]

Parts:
C1: 100u/16V; CP_Radial_D6.3mm_P2.50mm
C2: 10u; CP_Radial_D5.0mm_P2.00mm
C3, C4: 100n; C_Disc_D5.0mm_W2.5mm_P5.00mm
D1: LED_5V; LED_D3.0mm
H1, H2, H3, H4: M3; MountingHole_3.2mm_M3
J1: OLED_I2C; PinHeader_1x04_P2.54mm_Vertical
J2: GY-BMP280; PinHeader_1x06_P2.54mm_Vertical
J3: AM2302; PinHeader_1x03_P2.54mm_Vertical
J4: SDS011; PinHeader_1x04_P2.54mm_Vertical
J5: MQ135; PinHeader_1x04_P2.54mm_Vertical
J6: 5V_IN; TerminalBlock_Phoenix_MKDS-1,5-2-5.08_1x02_P5.08mm_Horizont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
J7: ESP32_Harness; PinHeader_1x12_P2.54mm_Vertical
JP1: VIN_LINK; PinHeader_1x02_P2.54mm_Vertical
JP_BEEP1: 3V3_5V_SEL; PinHeader_1x03_P2.54mm_Vertical
JP_PIR1: 3V3_5V_SEL; PinHeader_1x03_P2.54mm_Vertical
J_BEEP1: BEEPER; PinHeader_1x03_P2.54mm_Vertical
J_PIR1: D-SUN_PIR; PinHeader_1x03_P2.54mm_Vertical
J_VEML1: VEML7700; PinHeader_1x04_P2.54mm_Vertical
R1, R2: 10k; R_Axial_DIN0207_L6.3mm_D2.5mm_P7.62mm_Horizontal
R3: 15k; R_Axial_DIN0207_L6.3mm_D2.5mm_P7.62mm_Horizontal
R4, R5: 4k7; R_Axial_DIN0207_L6.3mm_D2.5mm_P7.62mm_Horizontal; not fitted
R6: 1k; R_Axial_DIN0207_L6.3mm_D2.5mm_P7.62mm_Horizontal
U1: ESP32_DevKit_V1_Socket; ESP32_DevKit_1x15x2_P25.40mm

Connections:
+3V3: C2.1, C3.1, J1.2, J2.1, J2.5, J3.1, J7.1, J7.12, JP_BEEP1.1, JP_PIR1.1, J_VEML1.1, R1.1, R4.1, R5.1, U1.30 (3V3)
+5V: C1.1, C4.1, J4.1, J5.1, J6.1, JP1.1, JP_BEEP1.3, JP_PIR1.3, R6.1
BEEP_SIG: J_BEEP1.3, U1.8 (GPIO25)
BEEP_VCC: JP_BEEP1.2, J_BEEP1.1
DHT_DATA: J3.2, J7.5, R1.2, U1.22 (GPIO18)
ESP_VIN: JP1.2, U1.15 (VIN)
GND: C1.2, C2.2, C3.2, C4.2, D1.1 (K), J1.1, J2.2, J2.6, J3.3, J4.2, J5.2, J6.2, J7.2, J7.11, J_BEEP1.2, J_PIR1.2, J_VEML1.2, R3.2, U1.14 (GND), U1.29 (GND)
LED_A: D1.2 (A), R6.2
MQ_ADC: J7.10, R2.2, R3.1, U1.4 (GPIO34)
MQ_AOUT: J5.3, R2.1
PIR_OUT: J_PIR1.3, U1.7 (GPIO33)
PIR_VCC: JP_PIR1.2, J_PIR1.1
PM_RX: J4.4, J7.9, U1.24 (GPIO17/TX2)
PM_TX: J4.3, J7.8, U1.25 (GPIO16/RX2)
SCL_LCD: J1.4, J7.3, U1.26 (GPIO4)
SCL_SENS: J2.3, J7.6, J_VEML1.3, R5.2, U1.21 (GPIO19)
SDA_LCD: J1.3, J7.4, U1.23 (GPIO5)
SDA_SENS: J2.4, J7.7, J_VEML1.4, R4.2, U1.20 (GPIO21)

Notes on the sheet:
AtmosMesh bench station - rev A Confirmed bench wiring (operator, 2026-08-14): OLED 0x3C SDA = GPIO5 SCL = GPIO4 VCC = 3V3 GY-BMP280 SDA = GPIO21 SCL = GPIO19 VCC = 3V3 CSB = 3V3 (I2C) SDO = GND (addr 0x76) AM2302/DHT22 DATA = GPIO18 (10k pull-up R1) VDD = 3V3 BEEPER SIG GPIO25 PIR D-SUN SIG GPIO33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

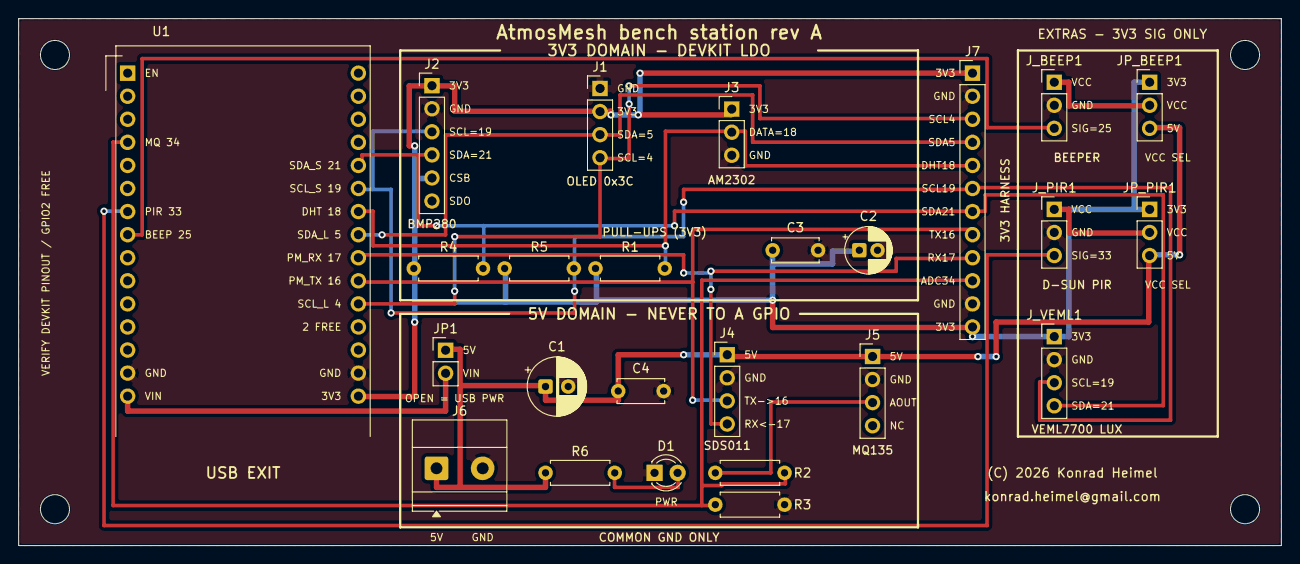
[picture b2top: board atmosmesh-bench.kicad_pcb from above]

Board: 2 copper layers, 139.0 x 58.0 mm, 29 parts (0 on the bottom side), 18 nets.

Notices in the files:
README.md:
License: MIT
hardware/kicad/atmosmesh-bench/atmosmesh-bench.kicad_pcb:
(C) 2026 Konrad Heimel
